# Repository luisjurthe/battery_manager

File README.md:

# battery_manager
Battery management system with high amp output.

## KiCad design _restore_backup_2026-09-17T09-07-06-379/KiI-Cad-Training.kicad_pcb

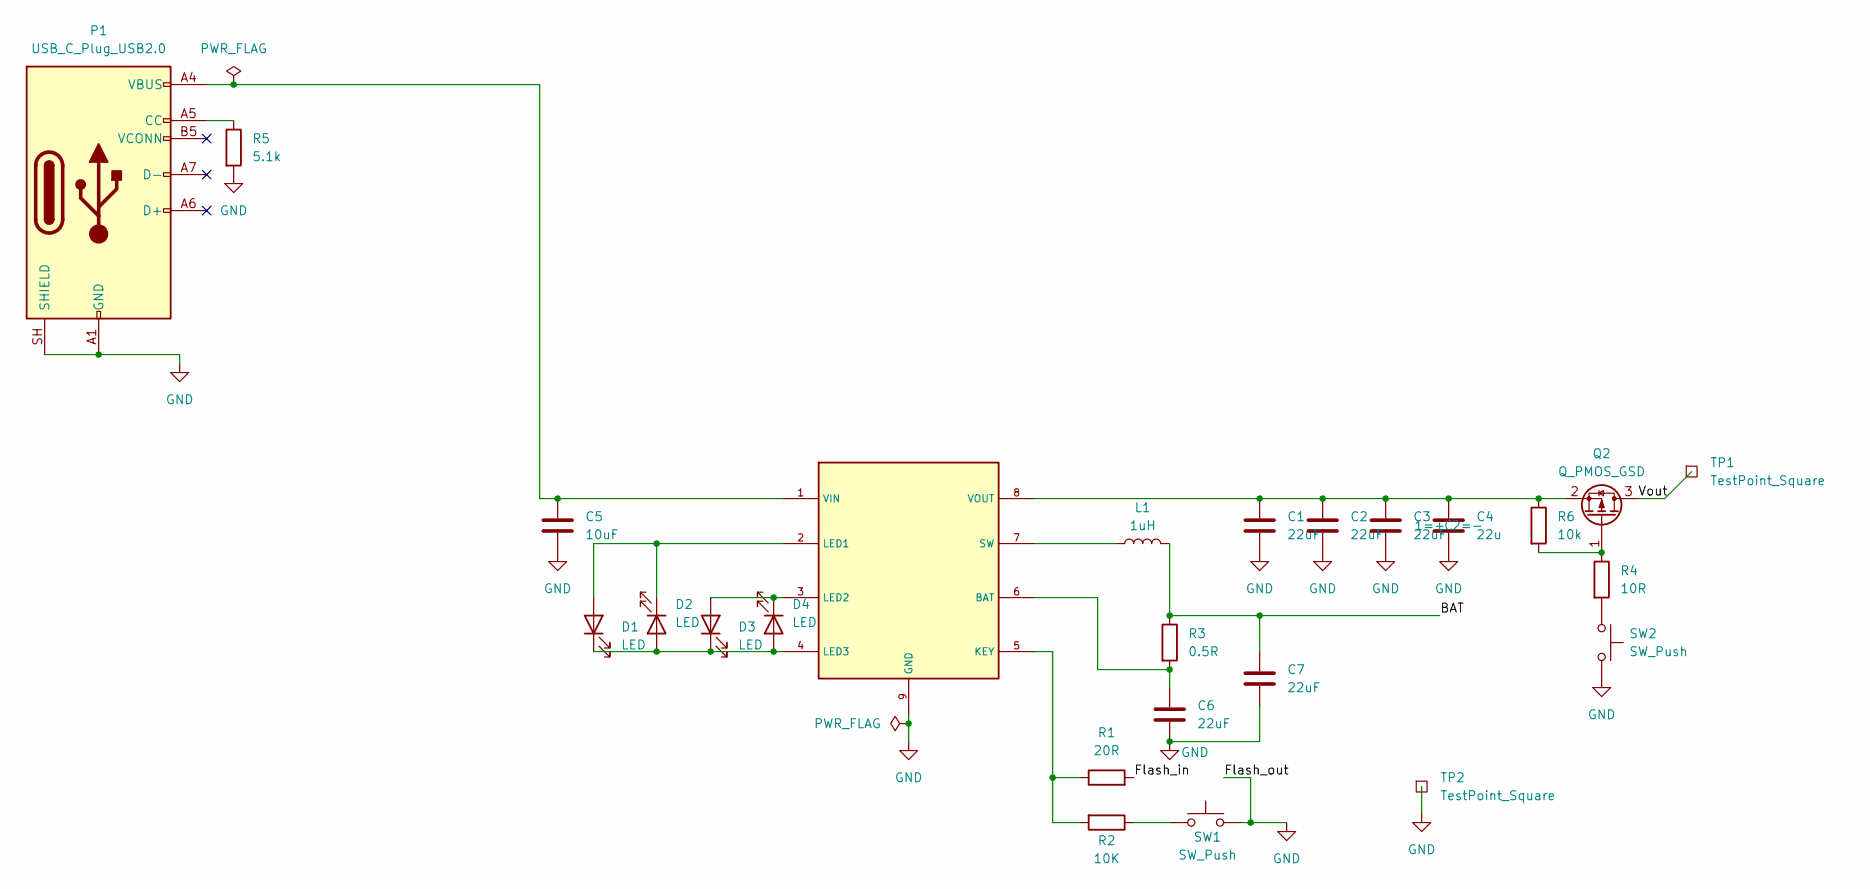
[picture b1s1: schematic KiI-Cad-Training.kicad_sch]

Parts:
C1, C2, C3, C6, C7: 22uF; C_Radial_D5.0mm_H11.0mm_P2.00mm
C4: 22u; C_Radial_D5.0mm_H11.0mm_P2.00mm
C5: 10uF; C_Radial_D6.3mm_H11.0mm_P2.50mm
D1, D2, D3, D4: LED; LED_Everlight-SMD3528_3.5x2.8mm_67-21ST
L1: 1uH; L_1008_2520Metric
P1: USB_C_Plug_USB2.0; USB_C_Receptacle_GCT_USB4105-xx-A_16P_TopMnt_Horizontal
Q2: Q_PMOS_GSD; SOT-23
R1: 20R; R_0603_1608Metric
R2: 10K; R_0603_1608Metric
R3: 0.5R; R_0603_1608Metric
R4: 10R; R_0603_1608Metric
R5: 5.1k; R_0603_1608Metric
R6: 10k; R_0603_1608Metric
SW1, SW2: SW_Push; SW_PUSH_6mm_H9.5mm
TP1, TP2: TestPoint_Square; TestPoint_Pad_2.5x2.5mm
U1: SOP127P600X165-9N

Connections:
/BAT: C7.1, L1.2, R3.1
/Flash_in: R1.2
/Vout: Q2.3 (D), TP1.1 (1_1)
GND: C1.2, C2.2, C3.2, C4.2, C5.2, C6.2, C7.2, P1.A1 (GND), P1.A12 (GND), P1.B1 (GND), P1.B12 (GND), P1.SH (SHIELD), R5.2, SW1.2, SW2.2, TP2.1 (1_1), U1.9 (GND)
unnamed: D1.2 (A), D2.1 (K), U1.2 (LED1)
unnamed: D1.1 (K), D2.2 (A), D3.1 (K), D4.2 (A), U1.4 (LED3)
unnamed: D3.2 (A), D4.1 (K), U1.3 (LED2)
unnamed: P1.A5 (CC), R5.1
unnamed: Q2.1 (G), R4.1, R6.2
unnamed: C1.1, C2.1, C3.1, C4.1, Q2.2 (S), R6.1, U1.8 (VOUT)
unnamed: R2.1, SW1.1
unnamed: R4.2, SW2.1
unnamed: C6.1, R3.2, U1.6 (BAT)
unnamed: R1.1, R2.2, U1.5 (KEY)
unnamed: L1.1, U1.7 (SW)
unnamed: C5.1, P1.A4 (VBUS), P1.A9 (VBUS), P1.B4 (VBUS), P1.B9 (VBUS), U1.1 (VIN)

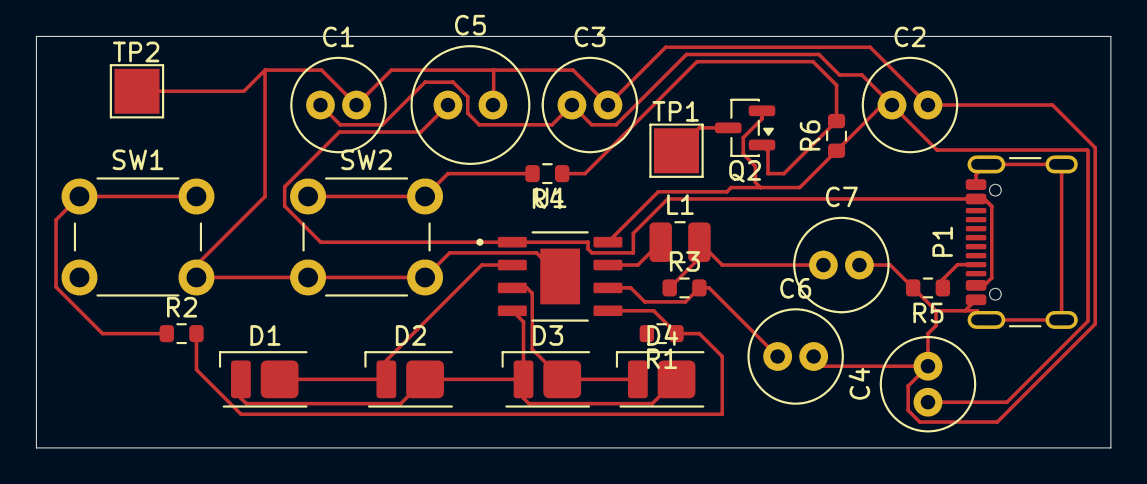
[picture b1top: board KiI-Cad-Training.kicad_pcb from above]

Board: 2 copper layers, 59.7 x 22.9 mm, 25 parts (0 on the bottom side), 15 nets.
